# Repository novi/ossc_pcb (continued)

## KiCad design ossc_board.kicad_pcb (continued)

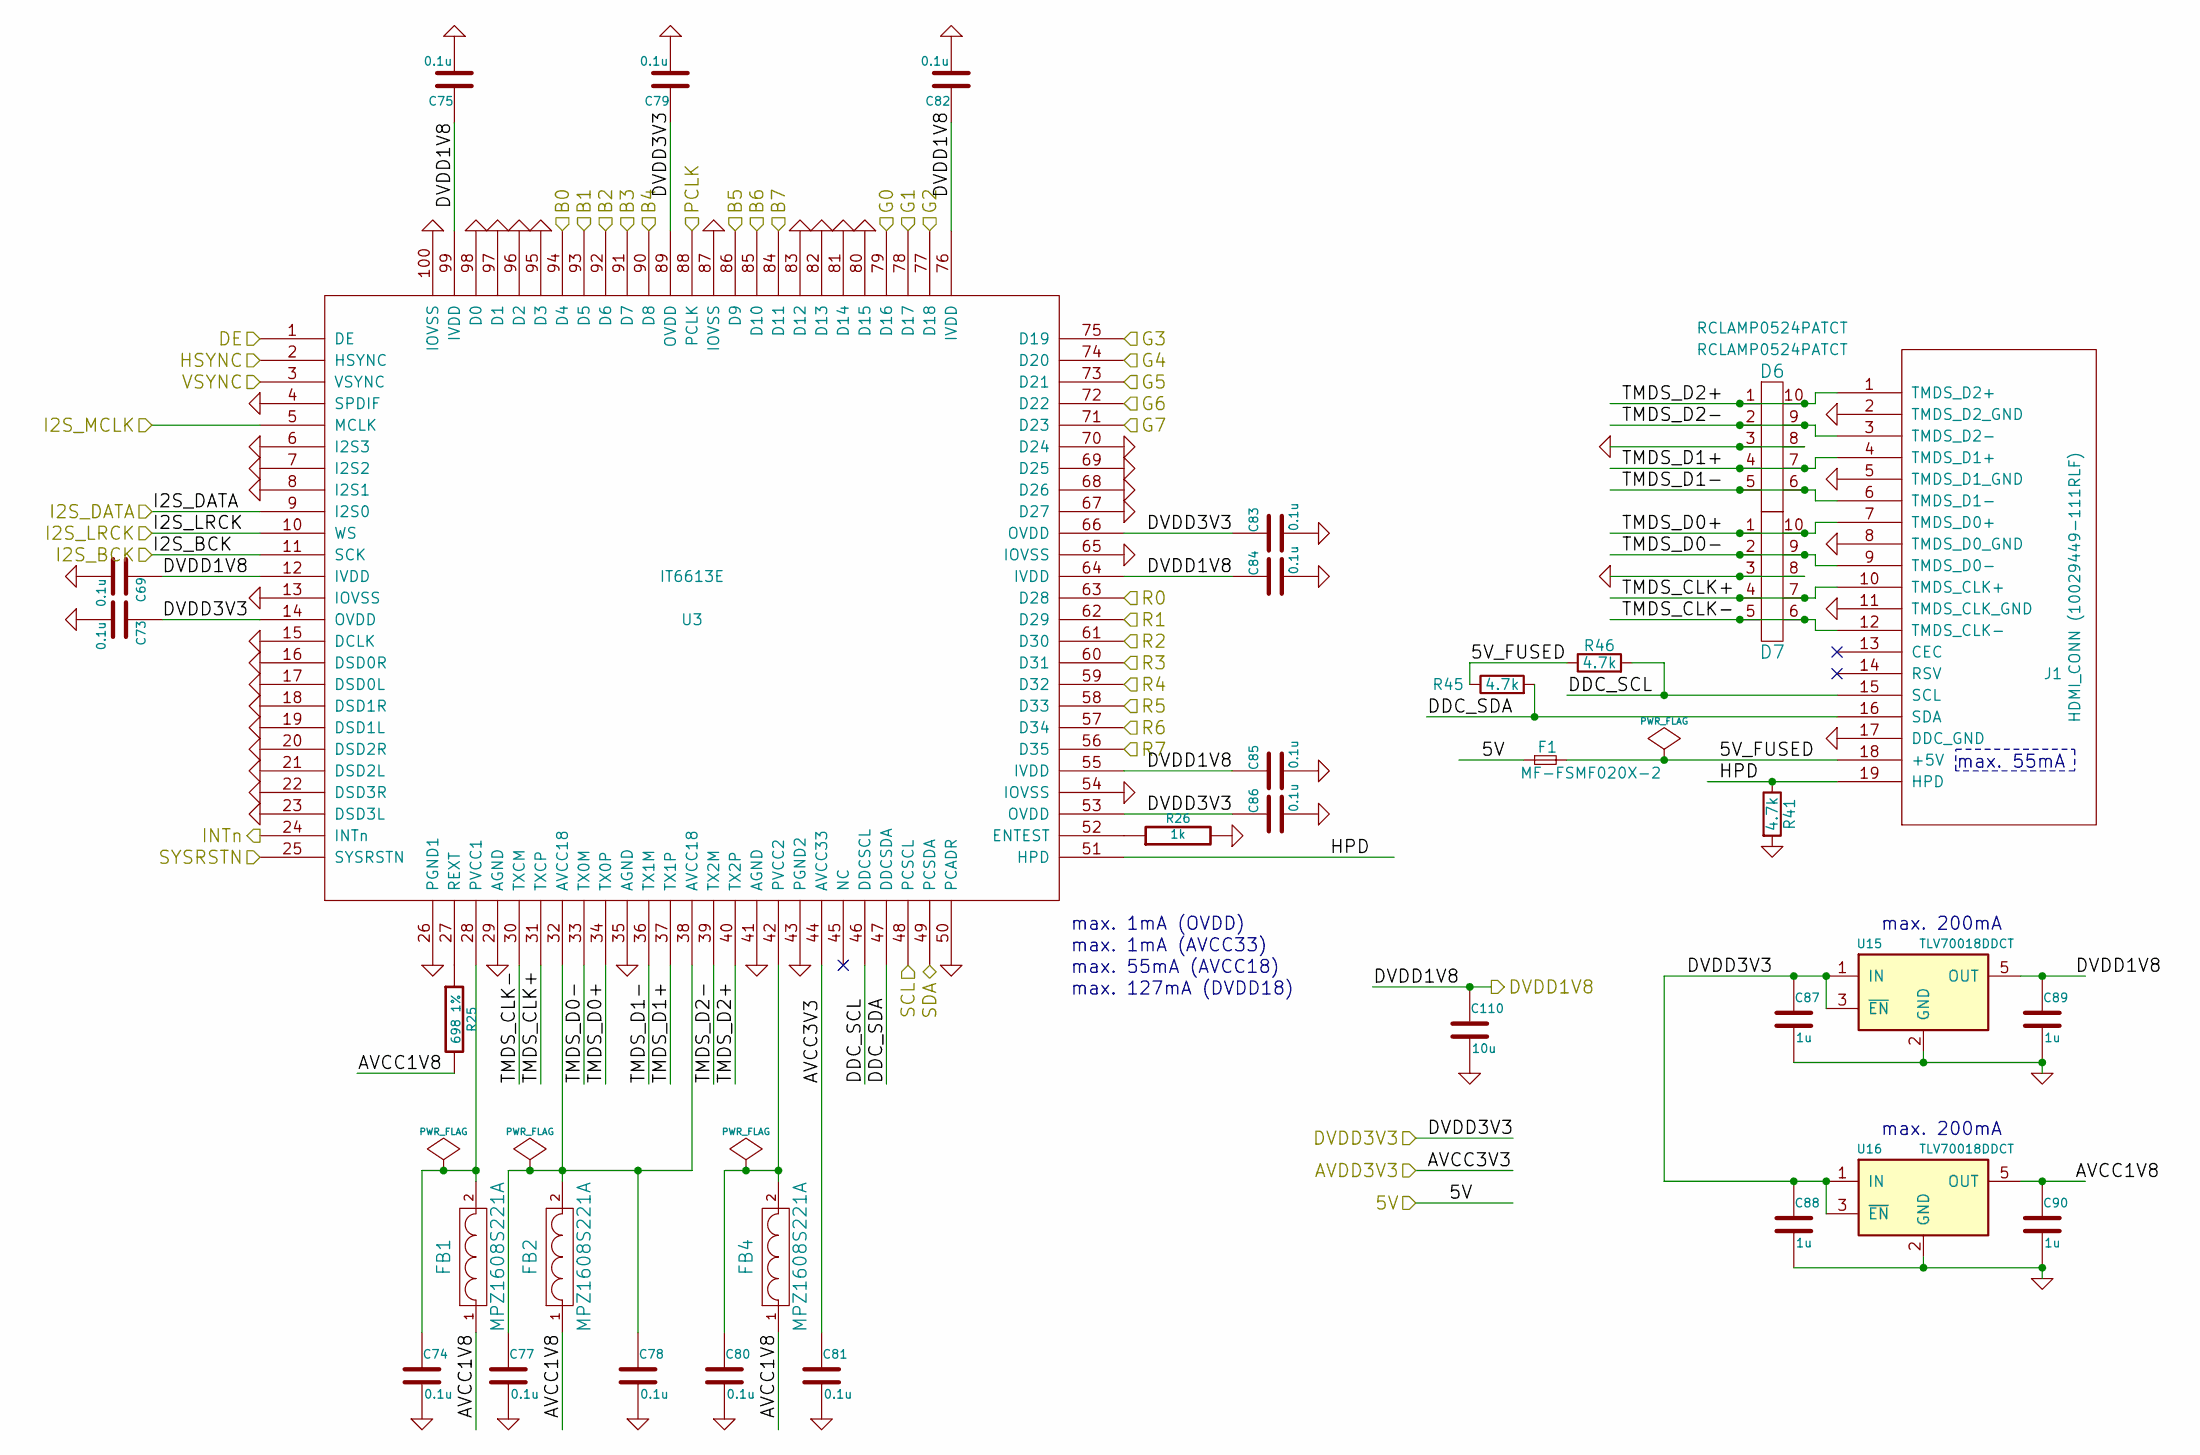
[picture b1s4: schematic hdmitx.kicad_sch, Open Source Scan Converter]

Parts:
C69, C73, C74, C75, C77, C78, C79, C80, C81, C82, C83, C84, C85, C86: 0.1u; C_0603_1608Metric_Pad1.05x0.95mm_HandSolder; Part ID GCJ188R71H104KA12D or GRM188R72A104MA35D
C87, C88, C89, C90: 1u; C_0603_1608Metric_Pad1.05x0.95mm_HandSolder; Part ID GRT188R61H105KE13D
C110: 10u; C_0603_1608Metric_Pad1.05x0.95mm_HandSolder; Part ID ZRB18AR61E106ME01L
D6, D7: RCLAMP0524PATCT; SLP2510P8
F1: MF-FSMF020X-2; L_0603_1608Metric_Pad1.05x0.95mm_HandSolder
FB1, FB2, FB4: MPZ1608S221A; L_0603_1608Metric_Pad1.05x0.95mm_HandSolder
J1: HDMI_CONN (10029449-111RLF); HDMI_CONN-10029449-111RLF; Part ID 10029449-111RLF
R25: 698 1%; R_0603_1608Metric_Pad1.05x0.95mm_HandSolder
R26: 1k; R_0603_1608Metric_Pad1.05x0.95mm_HandSolder
R41, R45, R46: 4.7k; R_0603_1608Metric_Pad1.05x0.95mm_HandSolder
U3: IT6613E; TQFP-100_custom
U15, U16: TLV70018DDCT; SOT-23-5_Handsoldering

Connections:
/fpga1/HDMITX_B0: U3.94 (D4); also elsewhere on the board
/fpga1/HDMITX_B1: U3.93 (D5); also elsewhere on the board
/fpga1/HDMITX_B2: U3.92 (D6); also elsewhere on the board
/fpga1/HDMITX_B3: U3.91 (D7); also elsewhere on the board
/fpga1/HDMITX_B4: U3.90 (D8); also elsewhere on the board
/fpga1/HDMITX_B5: U3.86 (D9); also elsewhere on the board
/fpga1/HDMITX_B6: U3.85 (D10); also elsewhere on the board
/fpga1/HDMITX_B7: U3.84 (D11); also elsewhere on the board
/fpga1/HDMITX_DE: U3.1 (DE); also elsewhere on the board
/fpga1/HDMITX_G0: U3.79 (D16); also elsewhere on the board
/fpga1/HDMITX_G1: U3.78 (D17); also elsewhere on the board
/fpga1/HDMITX_G2: U3.77 (D18); also elsewhere on the board
/fpga1/HDMITX_G3: U3.75 (D19); also elsewhere on the board
/fpga1/HDMITX_G4: U3.74 (D20); also elsewhere on the board
/fpga1/HDMITX_G5: U3.73 (D21); also elsewhere on the board
/fpga1/HDMITX_G6: U3.72 (D22); also elsewhere on the board
/fpga1/HDMITX_G7: U3.71 (D23); also elsewhere on the board
/fpga1/HDMITX_HSYNC: U3.2 (HSYNC); also elsewhere on the board
/fpga1/HDMITX_INT_N: U3.24 (INTn); also elsewhere on the board
/fpga1/HDMITX_PCLK: U3.88 (PCLK); also elsewhere on the board
/fpga1/HDMITX_R0: U3.63 (D28); also elsewhere on the board
/fpga1/HDMITX_R1: U3.62 (D29); also elsewhere on the board
/fpga1/HDMITX_R2: U3.61 (D30); also elsewhere on the board
/fpga1/HDMITX_R3: U3.60 (D31); also elsewhere on the board
/fpga1/HDMITX_R4: U3.59 (D32); also elsewhere on the board
/fpga1/HDMITX_R5: U3.58 (D33); also elsewhere on the board
/fpga1/HDMITX_R6: U3.57 (D34); also elsewhere on the board
/fpga1/HDMITX_R7: U3.56 (D35); also elsewhere on the board
/fpga1/HDMITX_VSYNC: U3.3 (VSYNC); also elsewhere on the board
/fpga1/RESET_N: U3.25 (SYSRSTN); also elsewhere on the board
/fpga1/SCL: U3.48 (PCSCL); also elsewhere on the board
/fpga1/SDA: U3.49 (PCSDA); also elsewhere on the board
/hdmitx1/5V: F1.1; also elsewhere on the board
/hdmitx1/5V_FUSED: F1.2, J1.18 (+5V), R45.1, R46.1
/hdmitx1/AVCC1V8: C90.1, FB1.1, FB2.1, FB4.1, R25.2, U16.5 (OUT)
/hdmitx1/AVCC3V3: C81.1, U3.44 (AVCC33); also elsewhere on the board
/hdmitx1/DDC_SCL: J1.15 (SCL), R46.2, U3.46 (DDCSCL)
/hdmitx1/DDC_SDA: J1.16 (SDA), R45.2, U3.47 (DDCSDA)
/hdmitx1/DVDD1V8: C69.1, C75.1, C82.1, C84.1, C85.1, C89.1, C110.1, U3.12 (IVDD), U3.55 (IVDD), U3.64 (IVDD), U3.76 (IVDD), U3.99 (IVDD), U15.5 (OUT); also elsewhere on the board
/hdmitx1/HPD: J1.19 (HPD), R41.1, U3.51 (HPD)
/hdmitx1/I2S_BCK: U3.11 (SCK); also elsewhere on the board
/hdmitx1/I2S_DATA: U3.9 (I2S0); also elsewhere on the board
/hdmitx1/I2S_LRCK: U3.10 (WS); also elsewhere on the board
/hdmitx1/TMDS_CLK+: D7.4, D7.7, J1.10 (TMDS_CLK+), U3.31 (TXCP)
/hdmitx1/TMDS_CLK-: D7.5, D7.6, J1.12 (TMDS_CLK-), U3.30 (TXCM)
/hdmitx1/TMDS_D0+: D7.1, D7.10, J1.7 (TMDS_D0+), U3.34 (TX0P)
/hdmitx1/TMDS_D0-: D7.2, D7.9, J1.9 (TMDS_D0-), U3.33 (TX0M)
/hdmitx1/TMDS_D1+: D6.4, D6.7, J1.4 (TMDS_D1+), U3.37 (TX1P)
/hdmitx1/TMDS_D1-: D6.5, D6.6, J1.6 (TMDS_D1-), U3.36 (TX1M)
/hdmitx1/TMDS_D2+: D6.1, D6.10, J1.1 (TMDS_D2+), U3.40 (TX2P)
/hdmitx1/TMDS_D2-: D6.2, D6.9, J1.3 (TMDS_D2-), U3.39 (TX2M)
/soundbox/MCLK: U3.5 (MCLK); also elsewhere on the board
GND: C69.2, C73.2, C74.2, C75.2, C77.2, C78.2, C79.2, C80.2, C81.2, C82.2, C83.2, C84.2, C85.2, C86.2, C87.2, C88.2, C89.2, C90.2, C110.2, D6.3, D6.8, D7.3, D7.8, J1.2 (TMDS_D2_GND), J1.5 (TMDS_D1_GND), J1.8 (TMDS_D0_GND), J1.11 (TMDS_CLK_GND), J1.17 (DDC_GND), R26.2, R41.2, U3.4 (SPDIF), U3.6 (I2S3), U3.7 (I2S2), U3.8 (I2S1), U3.13 (IOVSS), U3.15 (DCLK), U3.16 (DSD0R), U3.17 (DSD0L), U3.18 (DSD1R), U3.19 (DSD1L), U3.20 (DSD2R), U3.21 (DSD2L), U3.22 (DSD3R), U3.23 (DSD3L), U3.26 (PGND1), U3.29 (AGND), U3.35 (AGND), U3.41 (AGND), U3.43 (PGND2), U3.50 (PCADR), U3.54 (IOVSS), U3.65 (IOVSS), U3.67 (D27), U3.68 (D26), U3.69 (D25), U3.70 (D24), U3.80 (D15), U3.81 (D14), U3.82 (D13), U3.83 (D12), U3.87 (IOVSS), U3.95 (D3), U3.96 (D2), U3.97 (D1), U3.98 (D0), U3.100 (IOVSS), U15.2 (GND), U16.2 (GND); also elsewhere on the board
unnamed: C77.1, C78.1, FB2.2, U3.32 (AVCC18), U3.38 (AVCC18)
unnamed: R26.1, U3.52 (ENTEST)
unnamed: C74.1, FB1.2, U3.28 (PVCC1)
unnamed: C80.1, FB4.2, U3.42 (PVCC2)
unnamed: R25.1, U3.27 (REXT)
VCC: C73.1, C79.1, C83.1, C86.1, C87.1, C88.1, U3.14 (OVDD), U3.53 (OVDD), U3.66 (OVDD), U3.89 (OVDD), U15.1 (IN), U15.3 (~EN), U16.1 (IN), U16.3 (~EN); also elsewhere on the board

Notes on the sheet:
max. 127mA (DVDD18)
max. 55mA
max. 200mA
max. 55mA (AVCC18)
max. 1mA (OVDD)
max. 1mA (AVCC33)

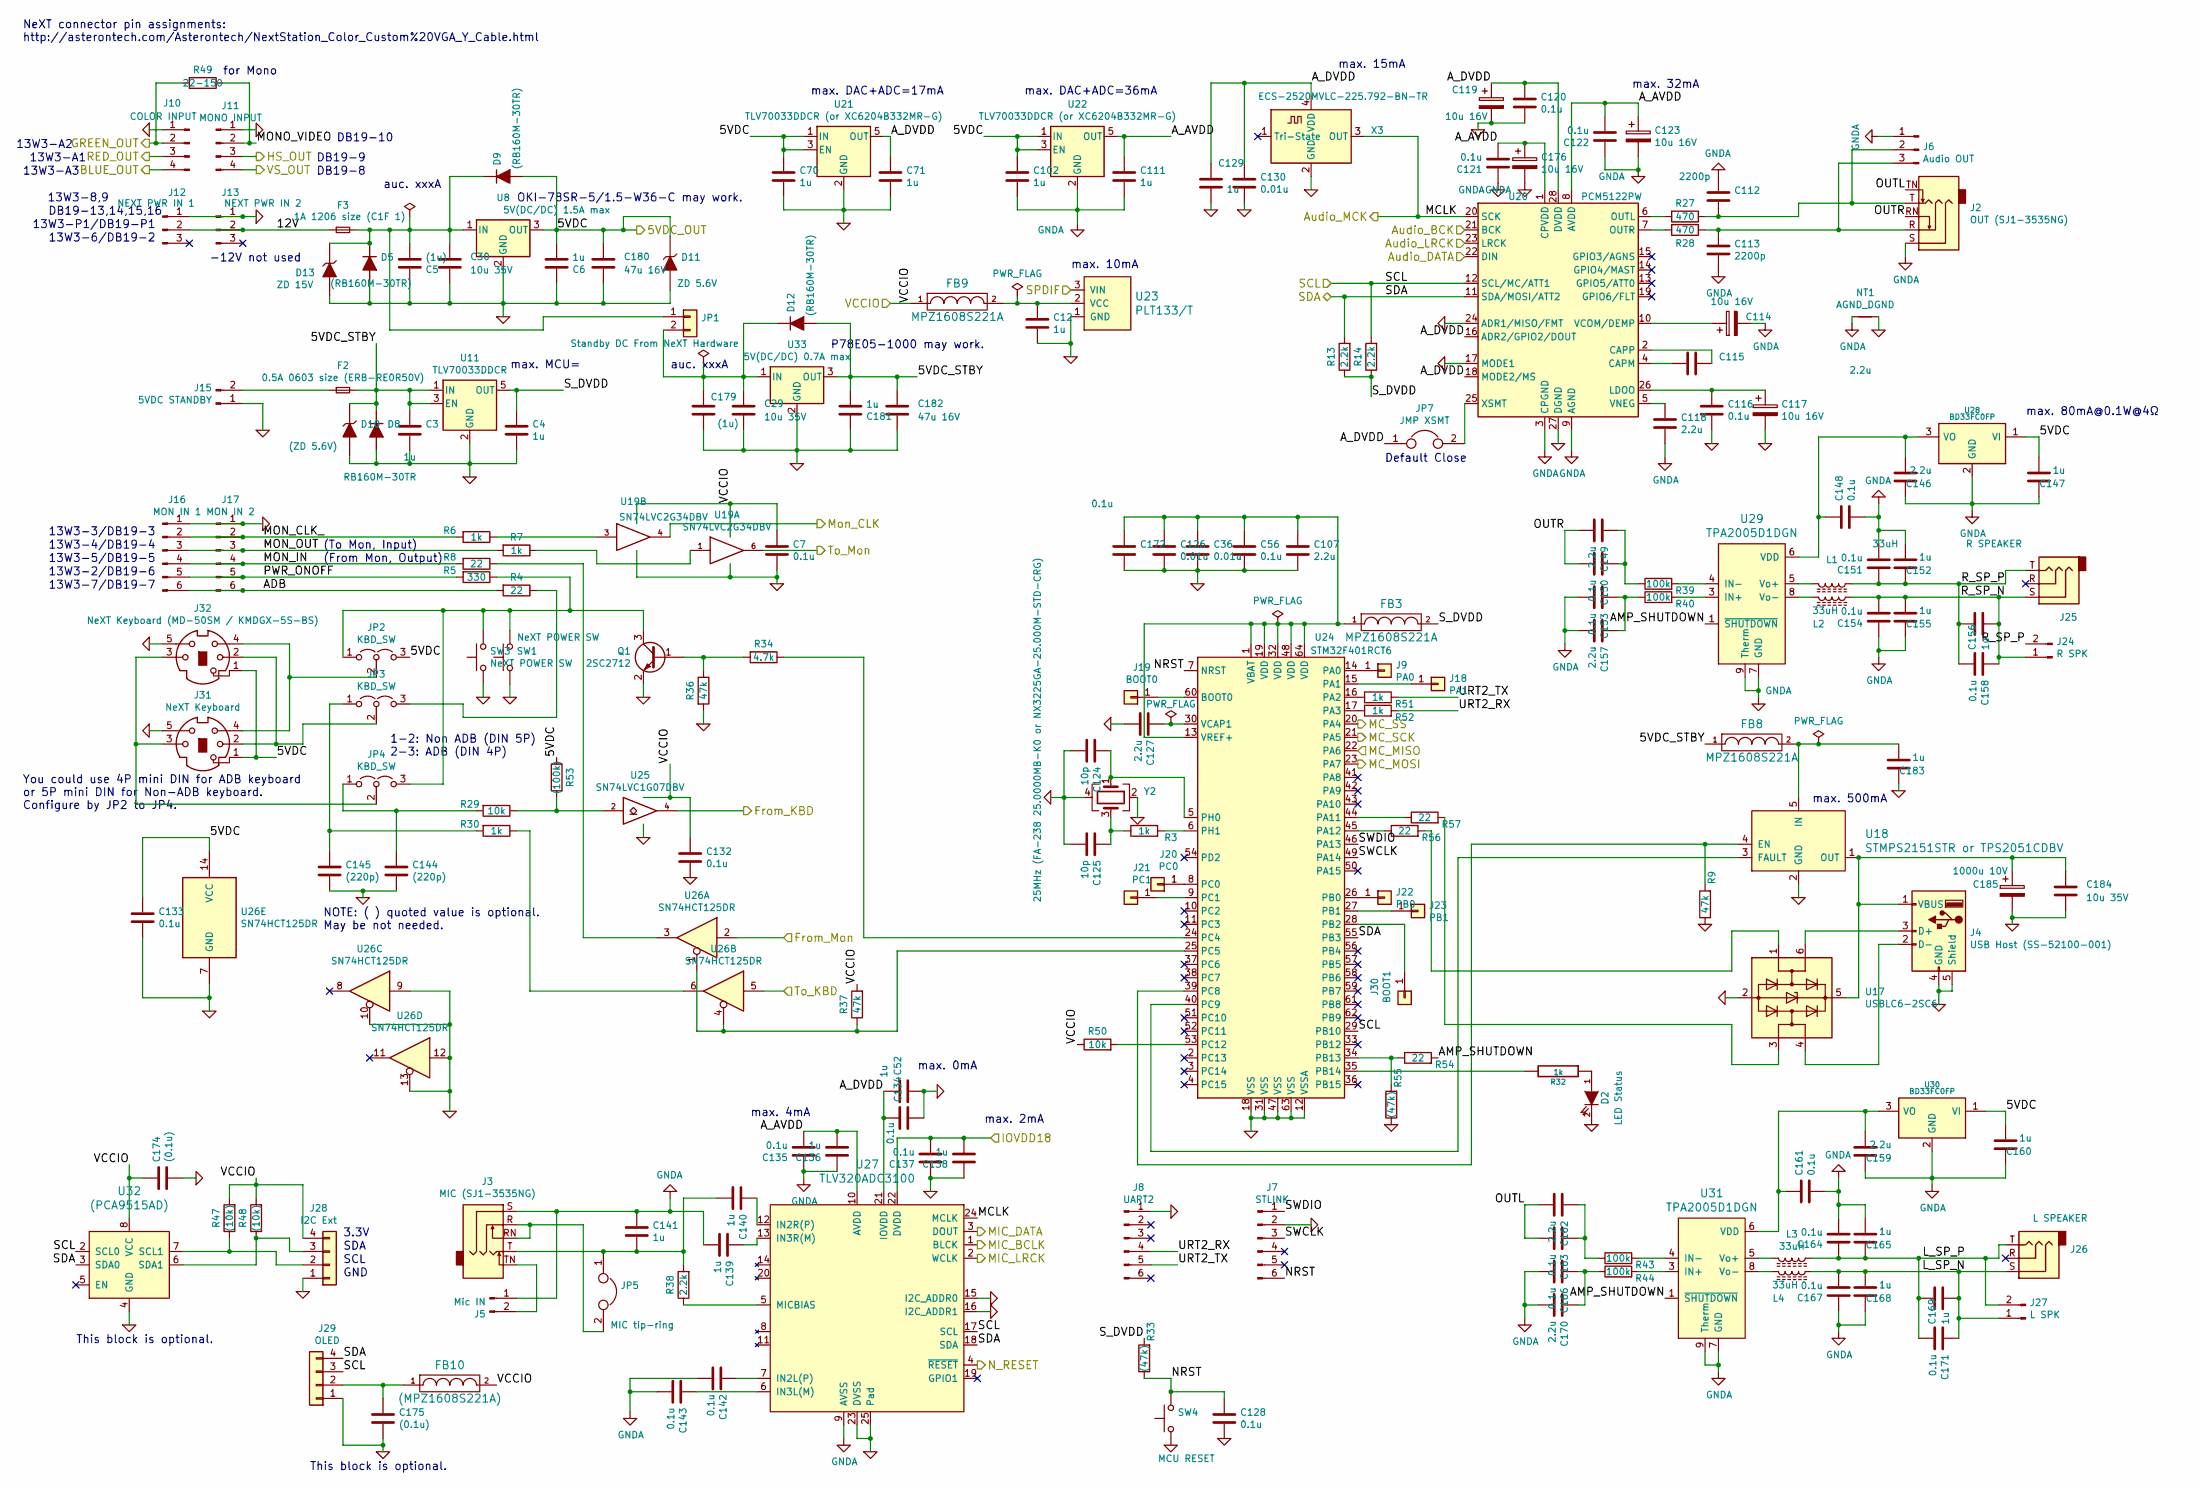
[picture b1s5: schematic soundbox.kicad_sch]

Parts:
C3, C4, C6, C12, C52, C70, C71, C102, C111, C129, C136, C138, C139, C140, C141, C147, C152, C155, C156, C160, C165, C168, C169, C181, C183: 1u; C_0603_1608Metric_Pad1.05x0.95mm_HandSolder; Part ID GRT188R61H105KE13D
C5, C179: (1u); C_0603_1608Metric_Pad1.08x0.95mm_HandSolder; Part ID GRT188R61H105KE13D
C7, C56, C116, C120, C121, C122, C128, C132, C133, C134, C135, C137, C142, C143, C148, C150, C151, C153, C154, C158, C161, C163, C164, C166, C167, C171, C172: 0.1u; C_0603_1608Metric_Pad1.05x0.95mm_HandSolder; Part ID GCJ188R71H104KA12D or GRM188R72A104MA35D
C29, C30, C184: 10u 35V; C_1210_3225Metric_Pad1.33x2.70mm_HandSolder; Part ID GRM32ER7YA106KA12
C36, C126, C130: 0.01u; C_0603_1608Metric_Pad1.05x0.95mm_HandSolder; Part ID GCM188R72A103KA37J
C107, C115, C118, C127, C146, C149, C157, C159, C162, C170: 2.2u; C_0603_1608Metric_Pad1.05x0.95mm_HandSolder; Part ID GRM188R71A225KE15D
C112, C113: 2200p; C_0603_1608Metric_Pad1.05x0.95mm_HandSolder; Part ID GRM1885C1H222JA01J
C114, C117, C119, C123, C176: 10u 16V; CP_Elec_4x4.5; Part ID EEE-FK1C100AR or HB Series
C124, C125: 10p; C_0603_1608Metric_Pad1.05x0.95mm_HandSolder
C144, C145: (220p); C_0603_1608Metric_Pad1.05x0.95mm_HandSolder
C174, C175: (0.1u); C_0603_1608Metric_Pad1.05x0.95mm_HandSolder
C180, C182: 47u 16V; C_1210_3225Metric_Pad1.33x2.70mm_HandSolder; Part ID GRM32EC81C476KE15L
C185: 1000u 10V; C_Disc_D8.0mm_W2.5mm_P5.00mm; Part ID 10WXA1000MEFC10X9
D2: LED Status; LED_D3.0mm_Horizontal_O1.27mm_Z6.0mm
D5, D9, D12: (RB160M-30TR); D_SOD-123_HandSoldering
D8: RB160M-30TR; D_SOD-123_HandSoldering
D10: (ZD 5.6V); D_SMB_Handsoldering; Part ID 1SMB5919BT3G
D11: ZD 5.6V; D_SMB_Handsoldering; Part ID 1SMB5919BT3G
D13: ZD 15V; D_SMA; Part ID 1SMB5919BT3G
F2: 0.5A 0603 size (ERB-RE0R50V); Fuse_0603_1608Metric_Pad1.05x0.95mm_HandSolder
F3: 1A 1206 size (C1F 1); Fuse_1206_3216Metric_Pad1.42x1.75mm_HandSolder
FB3, FB8, FB9: MPZ1608S221A; L_0603_1608Metric_Pad1.05x0.95mm_HandSolder
FB10: (MPZ1608S221A); L_0603_1608Metric_Pad1.05x0.95mm_HandSolder
J2: OUT (SJ1-3535NG); SJ1-3535NG
J3: MIC (SJ1-3535NG); SJ1-3535NG
J4: USB Host (SS-52100-001); USB_A_Stewart_SS-52100-001_Horizontal
J5: Mic IN; JST_XH_B2B-XH-A_1x02_P2.50mm_Vertical
J6: Audio OUT; JST_XH_B3B-XH-A_1x03_P2.50mm_Vertical
J7: STLINK; PinHeader_1x06_P2.54mm_Vertical
J8: UART2; PinHeader_1x06_P2.54mm_Vertical
J9: PA0; TestPad-D1.0mm
J10: COLOR INPUT; JST_XH_B4B-XH-A_1x04_P2.50mm_Vertical
J11: MONO INPUT; JST_XH_B4B-XH-A_1x04_P2.50mm_Vertical
J12: NEXT PWR IN 1; JST_XH_B3B-XH-A_1x03_P2.50mm_Vertical
J13: NEXT PWR IN 2; JST_XH_B3B-XH-A_1x03_P2.50mm_Vertical
J15: 5VDC STANDBY; JST_XH_B2B-XH-A_1x02_P2.50mm_Vertical
J16: MON IN 1; JST_XH_B6B-XH-A_1x06_P2.50mm_Vertical
J17: MON IN 2; JST_XH_B6B-XH-A_1x06_P2.50mm_Vertical
J18: PA1; TestPad-D1.0mm
J19: BOOT0; TestPad-D1.0mm
J20: PC0; TestPad-D1.0mm
J21: PC1; TestPad-D1.0mm
J22: PB0; TestPad-D1.0mm
J23: PB1; TestPad-D1.0mm
J24: R SPK; JST_XH_B2B-XH-A_1x02_P2.50mm_Vertical
J25: R SPEAKER; SJ-2509N; Part ID SJ-2509N
J26: L SPEAKER; SJ-2509N; Part ID SJ-2509N
J27: L SPK; JST_XH_B2B-XH-A_1x02_P2.50mm_Vertical
J28: I2C Ext; JST_XH_B4B-XH-A_1x04_P2.50mm_Vertical
J29: OLED; OLED_0.91inch_I2C
J30: BOOT1; TestPad-D1.0mm
J31: NeXT Keyboard; Mini_DIN_5P
J32: NeXT Keyboard (MD-50SM / KMDGX-5S-BS); Mini_DIN_5P; Part ID MD-50SM / KMDGX-5S-BS
JP1: Standby DC From NeXT Hardware; PinHeader_1x02_P2.54mm_Vertical
JP2, JP3, JP4: KBD_SW; SolderJumper-3_P1.3mm_Open_RoundedPad1.0x1.5mm_NumberLabels
JP5: MIC tip-ring; SolderJumper-2_P1.3mm_Open_RoundedPad1.0x1.5mm
JP7: JMP XSMT; SolderJumper-2_P1.3mm_Bridged_RoundedPad1.0x1.5mm
L1, L2, L3, L4: 33uH; L_TDK_SLF7045_HandSoldering; Part ID SLF7045T-330MR
NT1: AGND_DGND; NetTie-2_SMD_Pad2.0mm
Q1: 2SC2712; SC-59_Handsoldering
R3, R6, R7, R30, R32, R51, R52: 1k; R_0603_1608Metric_Pad1.05x0.95mm_HandSolder
R4, R8: 22; R_0603_1608Metric_Pad1.05x0.95mm_HandSolder
R5: 330; R_0603_1608Metric_Pad1.05x0.95mm_HandSolder
R9, R36, R37: 47k; R_0603_1608Metric_Pad1.05x0.95mm_HandSolder
R13, R14, R38: 2.2k; R_0603_1608Metric_Pad1.05x0.95mm_HandSolder
R27, R28: 470; R_0603_1608Metric_Pad1.05x0.95mm_HandSolder
R29, R50: 10k; R_0603_1608Metric_Pad1.05x0.95mm_HandSolder
R33: (47k); R_0603_1608Metric_Pad1.05x0.95mm_HandSolder
R34: 4.7k; R_0603_1608Metric_Pad1.05x0.95mm_HandSolder
R39, R40, R43, R44: 100k; R_0603_1608Metric_Pad1.05x0.95mm_HandSolder
R47, R48: (10k); R_0603_1608Metric_Pad1.05x0.95mm_HandSolder
R49: 22-150; R_0603_1608Metric_Pad1.05x0.95mm_HandSolder
R53: (100k); R_0603_1608Metric_Pad1.05x0.95mm_HandSolder
R54, R56, R57: 22; R_0603_1608Metric_Pad0.98x0.95mm_HandSolder
R55: (47k); R_0603_1608Metric_Pad0.98x0.95mm_HandSolder
SW1, SW3: NeXT POWER SW; SW_Tactile_SKHH_Angled; Part ID (1-1825027-1 / 2-1825027-0)
SW4: MCU RESET; SW_PUSH_6mm
U8: 5V(DC/DC) 1.5A max; TO-220-3_Vertical; Part ID OKI-78SR-5/1.5-W36-C
U11: TLV70033DDCR; SOT-23-5_Handsoldering
U17: USBLC6-2SC6; SOT-23-6_Handsoldering
U18: STMPS2151STR‎ or TPS2051CDBV; SOT-23-5_HandSoldering
U19: SN74LVC2G34DBV; SOT-23-6_Handsoldering
U20: PCM5122PW; TSSOP-28_4.4x9.7mm_P0.65mm
U21, U22: TLV70033DDCR (or XC6204B332MR-G); SOT-23-5_Handsoldering
U23: PLT133/T; PLT133_T
U24: STM32F401RCT6; LQFP-64_10x10mm_P0.5mm
U25: SN74LVC1G07DBV; SOT-23-5_HandSoldering
U26: SN74HCT125DR; SOIC-14_3.9x8.7mm_P1.27mm
U27: TLV320ADC3100; VQFN-24-1EP_4x4mm_P0.5mm_EP2.45x2.45mm
U28, U30: BD33FC0FP; TO-252-2
U29, U31: TPA2005D1DGN; MSOP-8-1EP_3x3mm_P0.65mm_EP1.73x1.85mm
U32: (PCA9515AD); SOIC-8_3.9x4.9mm_P1.27mm
U33: 5V(DC/DC) 0.7A max; TO-220-3_Vertical; Part ID P78E05-1000
X3: ECS-2520MVLC-225.792-BN-TR; Oscillator_SMD_SeikoEpson_SG210-4Pin_2.5x2.0mm_HandSoldering
Y2: 25MHz (FA-238 25.0000MB-K0 or NX3225GA-25.000M-ST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; Crystal_SMD_SeikoEpson_TSX3225-4Pin_3.2x2.5mm_HandSoldering

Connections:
/MC_MISO: U24.22 (PA6); also elsewhere on the board
/MC_MOSI: U24.23 (PA7); also elsewhere on the board
/MC_SCK: U24.21 (PA5); also elsewhere on the board
/MC_SS: U24.20 (PA4); also elsewhere on the board
/fpga1/BTN0: U25.4; also elsewhere on the board
/fpga1/FromMon: U26.2; also elsewhere on the board
/fpga1/LED0: U23.3 (VIN); also elsewhere on the board
/fpga1/Mic_BCLK: U27.1 (BLCK); also elsewhere on the board
/fpga1/Mic_Data: U27.3 (DOUT); also elsewhere on the board
/fpga1/Mic_LRCK: U27.2 (WCLK); also elsewhere on the board
/fpga1/MonCLKin: U19.4; also elsewhere on the board
/fpga1/RESET_N: U27.4 (~RESET); also elsewhere on the board
/fpga1/SCL: J29.3, R14.2, U20.12 (SCL/MC/ATT1), U24.29 (PB10), U27.17 (SCL), U32.2 (SCL0); also elsewhere on the board
/fpga1/SDA: J29.4, R13.2, U20.11 (SDA/MOSI/ATT2), U24.55 (PB3), U27.18 (SDA), U32.3 (SDA0); also elsewhere on the board
/fpga1/ToKBD: U26.5; also elsewhere on the board
/fpga1/ToMon: U19.6; also elsewhere on the board
/hdmitx1/5V: C6.2, C70.1, C102.1, C133.1, C147.2, C160.2, C180.1, D9.2 (A), D11.1 (K), J31.1, J32.1, JP2.3 (B), R53.2, U8.3 (OUT), U21.1 (IN), U21.3 (EN), U22.1 (IN), U22.3 (EN), U26.14 (VCC), U28.1 (VI), U30.1 (VI); also elsewhere on the board
/hdmitx1/DVDD1V8: C137.2, C138.2, U27.22 (DVDD); also elsewhere on the board
/hdmitx1/I2S_BCK: U20.21 (BCK); also elsewhere on the board
/hdmitx1/I2S_DATA: U20.22 (DIN); also elsewhere on the board
/hdmitx1/I2S_LRCK: U20.23 (LRCK); also elsewhere on the board
/soundbox/5VDC_STBY: C3.1, C181.2, C182.1, D8.1 (K), D10.1 (K), D12.2 (A), F2.2, FB8.1, U11.1 (IN), U11.3 (EN), U33.3 (OUT)
/soundbox/12V: F3.1, J12.2, J13.2
/soundbox/ADB: J16.6, J17.6, R4.2
/soundbox/AMP_SHUTDOWN: R54.2, U29.1 (~SHUTDOWN), U31.1 (~SHUTDOWN)
/soundbox/A_AVDD: C111.1, C121.2, C122.2, C123.1, C135.2, C136.2, C176.1, U20.1 (CPVDD), U20.8 (AVDD), U22.5 (OUT), U27.10 (AVDD)
/soundbox/A_DVDD: C52.1, C71.1, C119.1, C120.1, C129.1, C130.1, C134.1, JP7.1, U20.16 (ADR2/GPIO2/DOUT), U20.18 (MODE2/MS), U20.28 (DVDD), U21.5 (OUT), U27.21 (IOVDD), X3.4 (VDD)
/soundbox/L_SP_N: C167.2, C168.2, C169.2, C171.1, J26.S, J27.1, L4.1
/soundbox/L_SP_P: C164.1, C165.1, C169.1, C171.2, J26.T, J27.2, L3.1
/soundbox/MCLK: U20.20 (SCK), U27.24 (MCLK), X3.3 (OUT); also elsewhere on the board
/soundbox/MONO_VIDEO: J11.2, R49.1
/soundbox/MON_CLK_: J16.2, J17.2, R6.2
/soundbox/MON_IN: J16.4, J17.4, R8.2
/soundbox/MON_OUT: J16.3, J17.3, R7.2
/soundbox/NRST: C128.1, J7.6, R33.1, SW4.2, U24.7 (NRST)
/soundbox/OUTL: C162.2, C163.2, J2.TN
/soundbox/OUTR: C149.2, C150.2, J2.RN
/soundbox/PWR_ONOFF: J16.5, J17.5, R5.2
/soundbox/R_SP_N: C154.2, C155.2, C156.2, C158.1, J24.1, J25.S, L2.1
/soundbox/R_SP_P: C151.1, C152.1, C156.1, C158.2, J24.2, J25.T, L1.1
/soundbox/SWCLK: J7.3, U24.49 (PA14)
/soundbox/SWDIO: J7.1, U24.46 (PA13)
/soundbox/S_DVDD: C4.1, FB3.2, R13.1, R14.1, R33.2, U11.5 (OUT)
/soundbox/URT2_RX: J8.4, R52.2
/soundbox/URT2_TX: J8.5, R51.2
/tvp_board1/RGB3_B: J10.4; also elsewhere on the board
/tvp_board1/RGB3_G: J10.2, R49.2; also elsewhere on the board
/tvp_board1/RGB3_HS: J11.3; also elsewhere on the board
/tvp_board1/RGB3_R: J10.3; also elsewhere on the board
/tvp_board1/RGB3_VS: J11.4; also elsewhere on the board
GND: C3.2, C4.2, C5.1, C6.1, C7.2, C12.2, C29.2, C30.2, C36.2, C52.2, C56.2, C70.2, C71.2, C107.2, C116.2, C117.2, C119.2, C120.2, C124.2, C125.2, C126.2, C127.2, C128.2, C129.2, C130.2, C132.2, C133.2, C134.2, C137.1, C138.1, C144.2, C145.2, C172.2, C174.2, C175.2, C179.1, C180.2, C181.1, C182.2, C183.1, C184.2, C185.2, D2.2 (K), D5.2 (A), D8.2 (A), D10.2 (A), D11.2 (A), D13.2 (A), J4.4 (GND), J4.5 (Shield), J7.2, J8.1, J10.1, J11.1, J12.1, J13.1, J15.1, J16.1, J17.1, J28.1, J29.1, J31.5, J32.5, NT1.2, Q1.2 (E), R9.1, R36.2, R55.1, SW1.1, SW3.1, SW4.1, U8.2 (GND), U11.2 (GND), U17.2 (GND), U18.2 (GND), U19.2 (GND), U20.17 (MODE1), U20.24 (ADR1/MISO/FMT), U20.27 (DGND), U21.2 (GND), U23.1 (GND), U24.12 (VSSA), U24.18 (VSS), U24.31 (VSS), U24.47 (VSS), U24.63 (VSS), U25.3 (GND), U26.7 (GND), U26.9, U26.10, U26.12, U26.13, U27.15 (I2C_ADDR0), U27.16 (I2C_ADDR1), U27.23 (DVSS), U27.25 (Pad), U32.4 (GND), U33.2 (GND), X3.2 (GND), Y2.2, Y2.4; also elsewhere on the board
GNDA: C102.2, C111.2, C112.1, C113.2, C114.2, C118.2, C121.1, C122.1, C123.2, C135.1, C136.1, C139.2, C141.1, C142.2, C143.2, C146.1, C147.1, C148.2, C151.2, C152.2, C153.2, C154.1, C155.1, C157.2, C159.1, C160.1, C161.2, C164.2, C165.2, C166.2, C167.1, C168.1, C170.2, C176.2, J2.S, J3.S, J5.1, J6.1, NT1.1, U20.3 (CPGND), U20.9 (AGND), U22.2 (GND), U27.9 (AVSS), U28.2 (GND), U29.7 (GND), U29.9 (Therm), U30.2 (GND), U31.7 (GND), U31.9 (Therm)
unnamed: C125.1, R3.1, Y2.3
unnamed: C140.2, C141.2, J3.T, JP5.1, R38.2
unnamed: C149.1, C150.1, R39.1
unnamed: C153.1, C157.1, R40.1
unnamed: C162.1, C163.1, R43.1
unnamed: C166.1, C170.1, R44.1
unnamed: D2.1 (A), R32.1
unnamed: C29.1, C179.2, D12.1 (K), JP1.2, U33.1 (IN)
unnamed: C5.2, C30.1, D5.1 (K), D9.1 (K), D13.1 (K), F3.2, JP1.1, U8.1 (IN)
unnamed: J3.R, J3.RN, JP5.2
unnamed: J4.3 (D+), U17.6 (I/O1)
unnamed: J4.2 (D-), U17.4 (I/O2)
unnamed: C184.1, C185.1, J4.1 (VBUS), U17.5 (VBUS), U18.1 (OUT)
unnamed: J3.TN, J5.2
unnamed: C112.2, J2.T, J6.2, R27.1
unnamed: C113.1, J2.R, J6.3, R28.1
unnamed: J9.1 (Pin_1_1), U24.14 (PA0)
unnamed: F2.1, J15.2
unnamed: J18.1 (Pin_1_1), U24.15 (PA1)
unnamed: J19.1 (Pin_1_1), U24.60 (BOOT0)
unnamed: J20.1 (Pin_1_1), U24.8 (PC0)
unnamed: J21.1 (Pin_1_1), U24.9 (PC1)
unnamed: J22.1 (Pin_1_1), U24.26 (PB0)
unnamed: J23.1 (Pin_1_1), U24.27 (PB1)
unnamed: J28.2, R47.1, U32.7 (SCL1)
unnamed: J28.3, R48.1, U32.6 (SDA1)
unnamed: C175.1, FB10.1, J29.2
unnamed: J30.1 (Pin_1_1), U24.28 (PB2)
unnamed: JP2.1 (A), JP4.3 (B), Q1.3 (C), R5.1, SW1.2, SW3.2
unnamed: J31.4, J32.4, JP2.2 (C)
unnamed: C145.1, JP3.1 (A), R30.2
unnamed: JP3.3 (B), R4.1
unnamed: J31.2, J32.2, JP3.2 (C)
unnamed: C144.1, JP4.1 (A), R29.2
unnamed: J31.3, J32.3, JP4.2 (C)
unnamed: Q1.1 (B), R34.2, R36.1
unnamed: R6.1, U19.3
unnamed: R7.1, U19.1
unnamed: R8.1, U26.3
unnamed: R29.1, R53.1, U25.2
unnamed: R30.1, U26.6
unnamed: R56.2, U17.1 (I/O1)
unnamed: R57.2, U17.3 (I/O2)
unnamed: R9.2, U18.4 (EN), U24.39 (PC8)
unnamed: U18.3 (FAULT), U24.40 (PC9)
unnamed: C183.2, FB8.2, U18.5 (IN)
unnamed: C115.1, U20.4 (CAPM)
unnamed: C115.2, U20.2 (CAPP)
unnamed: C116.1, C117.1, U20.26 (LDOO)
unnamed: R27.2, U20.6 (OUTL)
unnamed: R28.2, U20.7 (OUTR)
unnamed: C114.1, U20.10 (VCOM/DEMP)
unnamed: C118.1, U20.5 (VNEG)
unnamed: JP7.2, U20.25 (XSMT)
unnamed: C12.1, FB9.2, U23.2 (VCC)
unnamed: R51.1, U24.16 (PA2)
unnamed: R52.1, U24.17 (PA3)
unnamed: R57.1, U24.44 (PA11)
unnamed: R56.1, U24.45 (PA12)
unnamed: R54.1, R55.2, U24.34 (PB13)
unnamed: R32.2, U24.35 (PB14)
unnamed: R34.1, U24.24 (PC4)
unnamed: R37.1, U24.25 (PC5), U26.1, U26.4
unnamed: R50.2, U24.53 (PC12)
unnamed: C124.1, U24.5 (PH0), Y2.1
unnamed: R3.2, U24.6 (PH1)
unnamed: C36.1, C56.1, C107.1, C126.1, C172.1, FB3.1, U24.1 (VBAT), U24.13 (VREF+), U24.19 (VDD), U24.32 (VDD), U24.48 (VDD), U24.64 (VDD)
unnamed: C127.1, U24.30 (VCAP1)
unnamed: C142.1, U27.7 (IN2L(P))
unnamed: C140.1, U27.12 (IN2R(P))
unnamed: C143.1, U27.6 (IN3L(M))
unnamed: C139.1, U27.13 (IN3R(M))
unnamed: R38.1, U27.5 (MICBIAS)
unnamed: C146.2, C148.1, U28.3 (VO), U29.6 (VDD)
unnamed: R40.2, U29.3 (IN+)
unnamed: R39.2, U29.4 (IN-)
unnamed: L1.2, U29.5 (Vo+)
unnamed: L2.2, U29.8 (Vo-)
unnamed: C159.2, C161.1, U30.3 (VO), U31.6 (VDD)
unnamed: R44.2, U31.3 (IN+)
unnamed: R43.2, U31.4 (IN-)
unnamed: L3.2, U31.5 (Vo+)
unnamed: L4.2, U31.8 (Vo-)
VCC: C7.1, C132.1, C174.1, FB9.1, FB10.2, J28.4, R37.2, R47.2, R48.2, R50.1, U19.5 (VCC), U25.5 (VCC), U32.8 (VCC); also elsewhere on the board

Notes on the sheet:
13W3-A3
13W3-4/DB19-4
OKI-78SR-5/1.5-W36-C may work.
13W3-A1
-12V not used
auc. xxxA
max. 2mA
max. 4mA
DB19-8
13W3-3/DB19-3
NOTE: ( ) quoted value is optional. May be not needed.
13W3-P1/DB19-P1
DB19-9
SCL
(To Mon, Input)
(From Mon, Output)
13W3-5/DB19-5
max. DAC+ADC=17mA
P78E05-1000 may work.
13W3-6/DB19-2
DB19-10
max. 10mA
13W3-2/DB19-6
max. 0mA
max. MCU=
NeXT connector pin assignments: http://asterontech.com/Asterontech/NextStation_Color_Custom%20VGA_Y_Cable.html
for Mono
max. 500mA
You could use 4P mini DIN for ADB keyboard or 5P mini DIN for Non-ADB keyboard. Configure by JP2 to JP4.
13W3-8,9
This block is optional.
DB19-13,14,15,16
13W3-7/DB19-7
max. 15mA
max. 32mA
GND
13W3-A2
SDA
max. DAC+ADC=36mA
max. 80mA@0.1W@4Ω

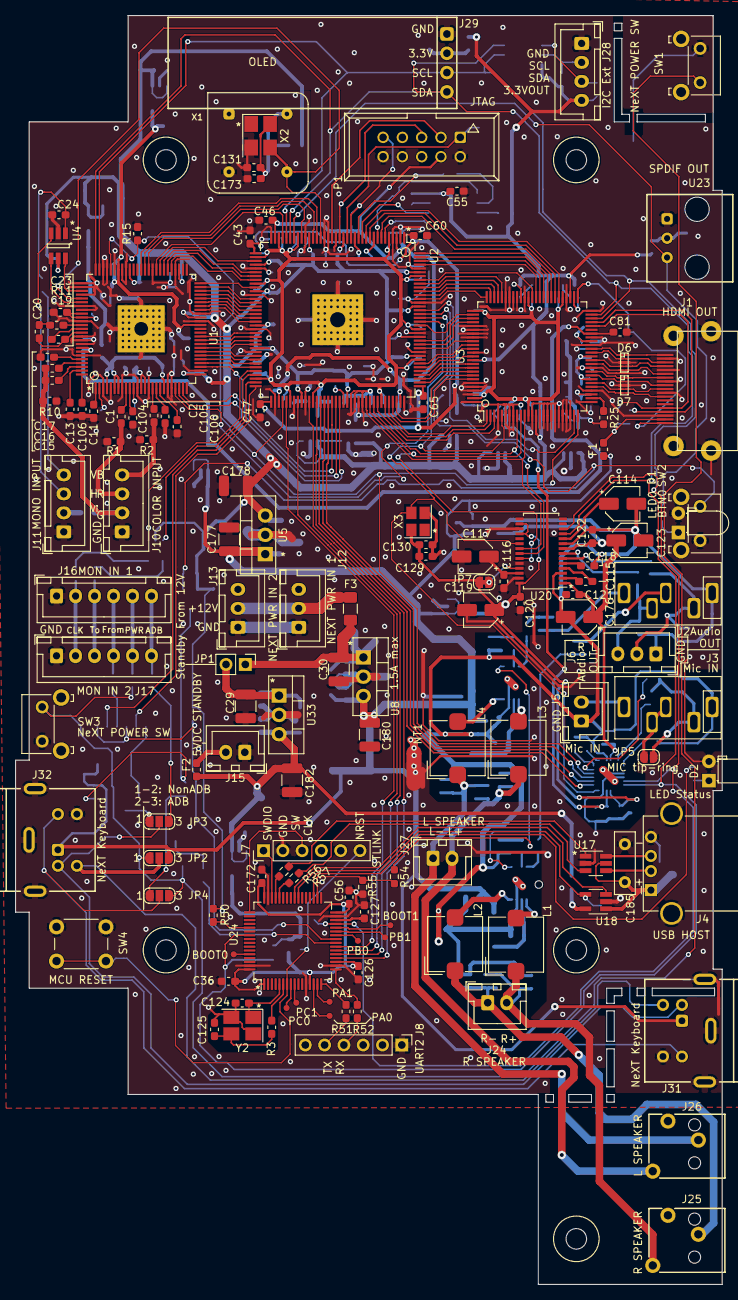
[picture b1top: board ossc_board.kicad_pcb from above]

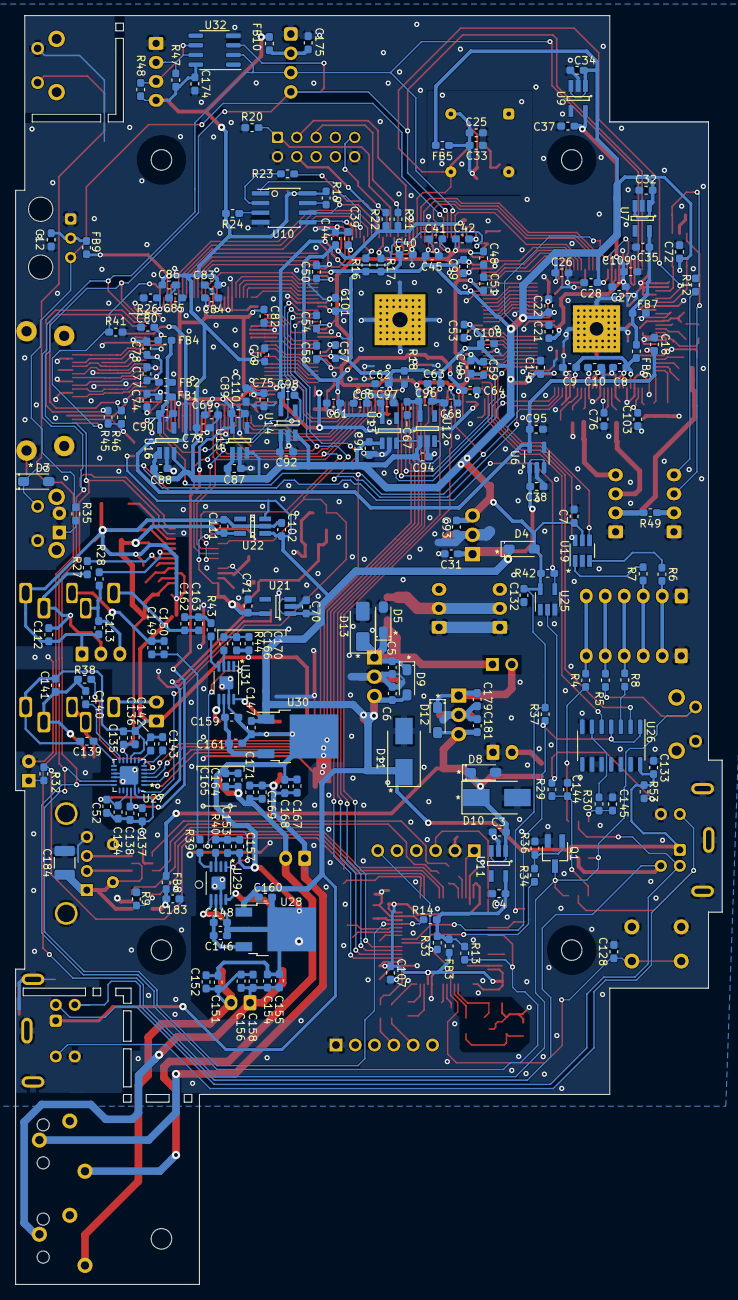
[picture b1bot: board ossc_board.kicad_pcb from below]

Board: 2 copper layers, 93.0 x 167.0 mm, 358 parts (217 on the bottom side), 256 nets.

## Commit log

2020-05-23 add test pins fix tracks
2020-05-23 minor fix
2020-05-24 generate gerber
2020-05-24 convert mechanical hole of the RGB connector into NPTH
2020-07-25 remove unnecessary component
2020-07-25 update the tracks
2020-07-26 update PCB
2020-07-27 update PCB 2
2020-07-29 update3
2020-07-29 minor update
2020-08-09 add dxf update pcb
2020-08-11 add adc
2020-08-16 update part no
2020-08-18 update tracks
2020-08-24 add more tracks
2020-08-26 update ground
2020-08-26 finish tracks
2020-08-27 add optional components
2020-09-01 update values
2020-09-07 rearrange FPGA pins
2020-09-07 update 2.5mm jack
2020-09-07 update MINI DIN
2020-09-10 update position
2020-09-12 fix wrong connection
2020-09-13 minor track update
2020-09-13 remove old gerber
2020-09-13 export gerber
2020-09-13 NeXT Sound Box function (1st rev) (#1)
2020-09-16 add uart registors
2020-09-21 add BOOT1 pad
2020-10-04 connect XSMT (errata)
2020-10-13 add protection zener
2020-10-15 update crystal pattern
2021-02-01 update mic lines
2021-02-15 update zone
2021-03-13 update value
2021-03-13 add cube ext card base dimensions
2021-03-13 move keyboard DIN connector
2021-03-22 update cube sound box dimensions
2021-03-27 update silk update mount plate
2021-04-06 update dimension for cube sound box plate
2021-05-24 change 3.3V liner regulator
2021-05-25 move front ADB connector treat shutdown pin of the amplifier
2021-05-28 add base enclosure dxf
2021-05-28 value update
2021-05-28 add comment
2021-05-28 update dxf
2021-05-28 front panel
2021-05-31 add caps
2021-06-02 add back panel outline
2021-06-05 fix2
2021-06-05 plot gerber
2021-06-16 add register for usb impedance matching
2021-06-25 fix silk
2021-07-06 add new mount plate
2021-07-11 update plate
2021-07-15 update register value
2021-07-17 update case
2021-07-30 notes added
2021-08-03 add BOM for the Sound Box
2022-03-17 update part
2022-03-19 migrated to KiCad 6
2024-05-17 migrated to KiCad 7
2024-05-17 DRC check and fix
2024-05-18 change capacitors
2026-04-06 migrate to KiCad 10
2026-04-06 add zener diode
2026-04-06 fix error
2026-04-06 fix DRC rule
